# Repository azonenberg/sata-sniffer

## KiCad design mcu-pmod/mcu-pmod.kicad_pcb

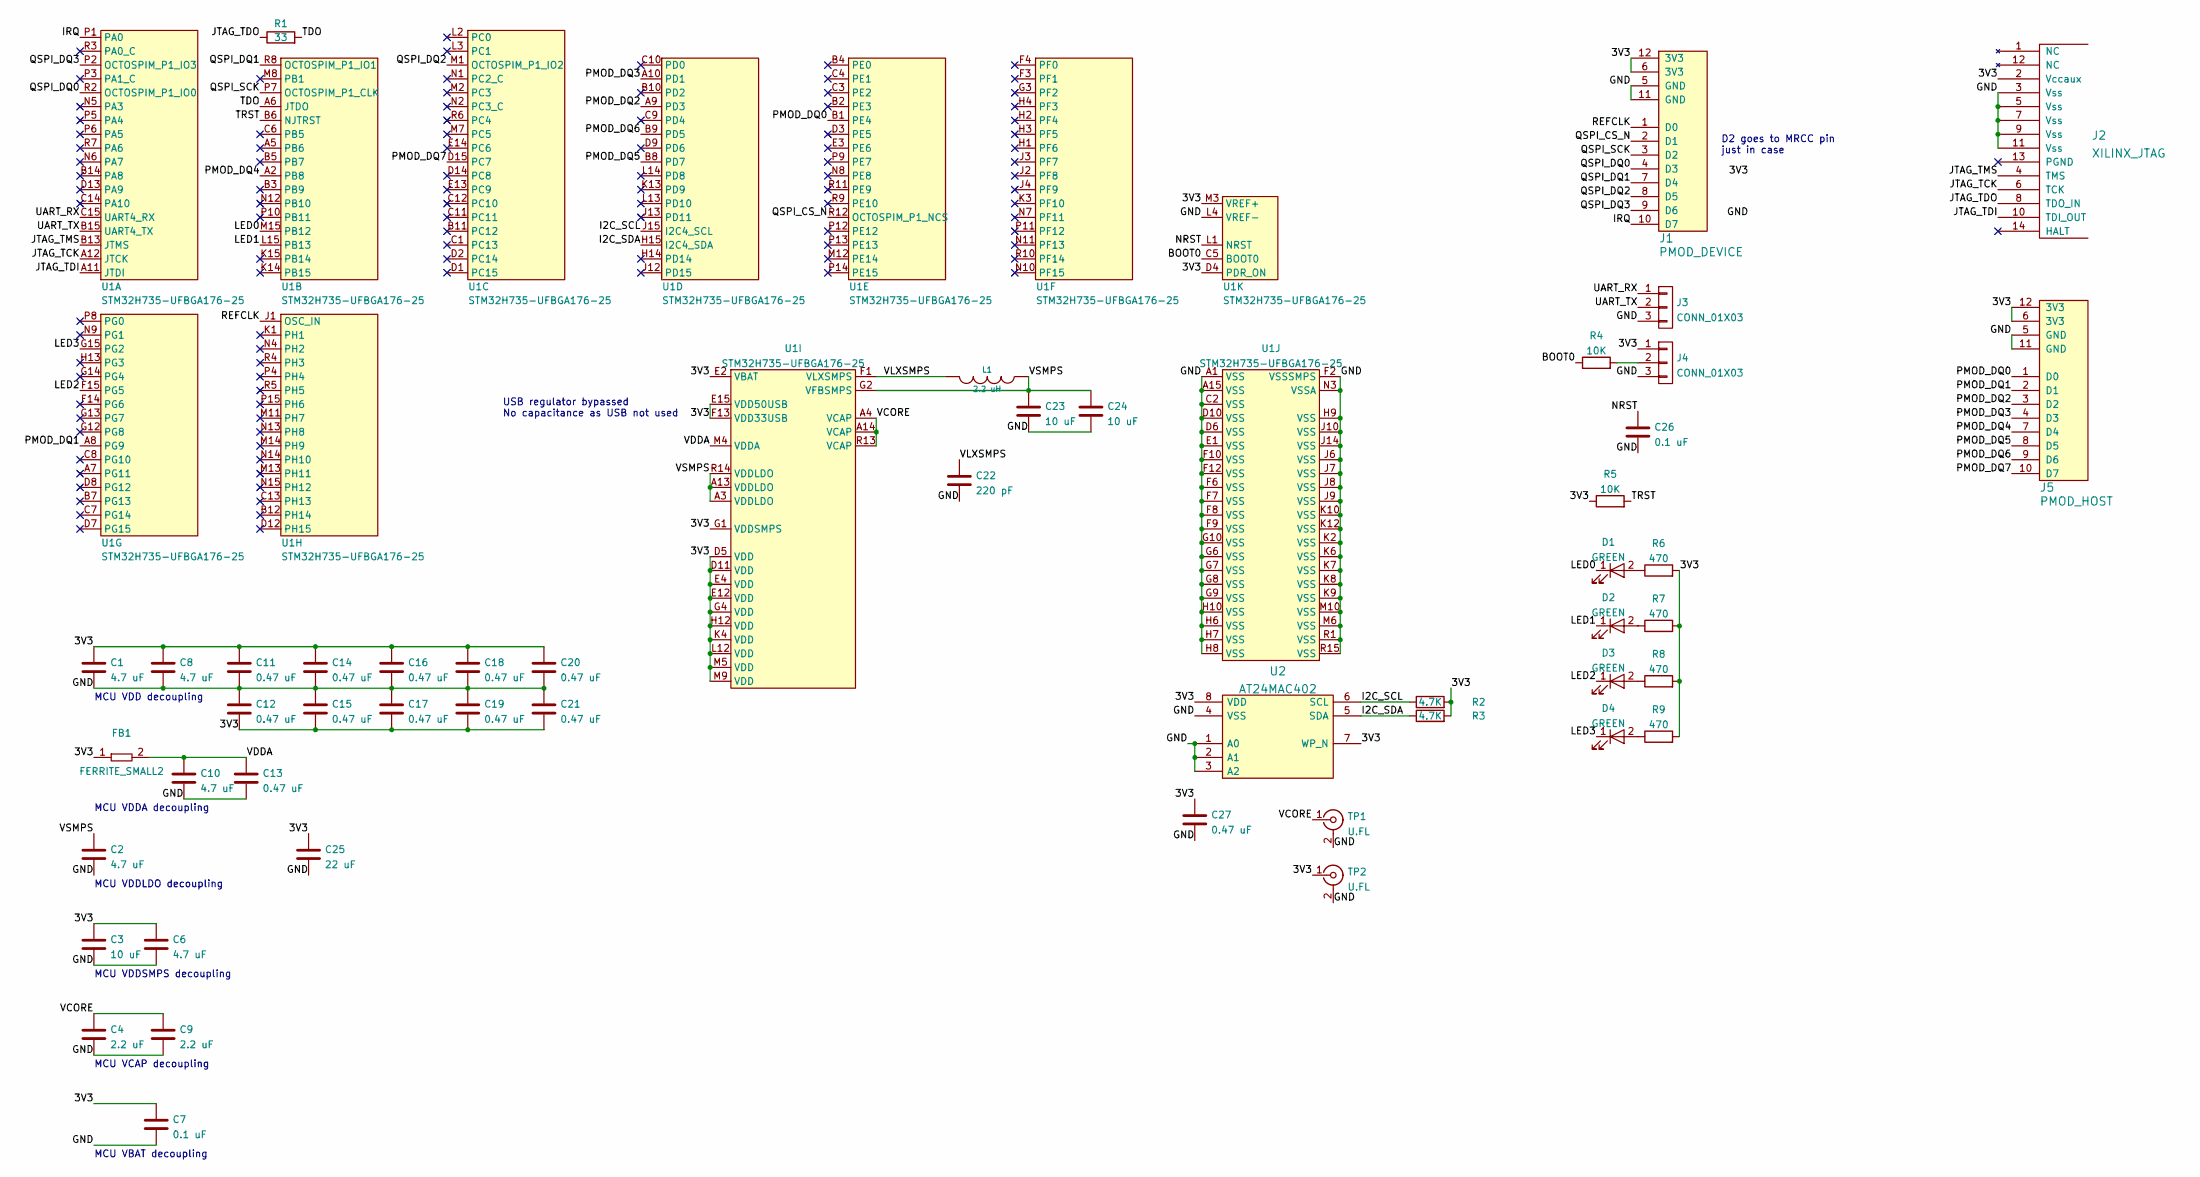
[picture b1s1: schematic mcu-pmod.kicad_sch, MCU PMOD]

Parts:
C1, C2, C6, C8, C10: 4.7 uF; EIA_0603_CAP_NOSILK
C3, C23, C24: 10 uF; EIA_0805_CAP_NOSILK
C4, C9: 2.2 uF; EIA_0603_CAP_NOSILK
C7, C26: 0.1 uF; EIA_0402_CAP_NOSILK
C11, C12, C13, C14, C15, C16, C17, C18, C19, C20, C21, C27: 0.47 uF; EIA_0402_CAP_NOSILK
C22: 220 pF; EIA_0402_CAP_NOSILK
C25: 22 uF; EIA_1206_CAP_NOSILK
D1, D2, D3, D4: GREEN; EIA_0805_LED
FB1: FERRITE_SMALL2; EIA_0603_INDUCTOR_NOSILK
J1: PMOD_DEVICE; CONN_HEADER_2.54MM_2x6_RA_PMOD_MODULE
J2: XILINX_JTAG; XILINX_JTAG_PTH_MOLEX_0878311420
J3, J4: CONN_01X03; CONN_HEADER_2.54MM_1x3
J5: PMOD_HOST; CONN_HEADER_2.54MM_2x6_RA_PMOD_HOST
L1: 2.2 uH; EIA_1210_CAP_NOSILK
R1: 33; EIA_0402_RES_NOSILK
R2, R3: 4.7K; EIA_0402_RES_NOSILK
R4, R5: 10K; EIA_0402_RES_NOSILK
R6, R7, R8, R9: 470; EIA_0402_RES_NOSILK
TP1, TP2: U.FL; CONN_U.FL_TE_1909763-1
U1: STM32H735-UFBGA176-25; BGA_201_10x10_DEPOP_0.65MM_OSHPARK
U2: AT24MAC402; DFN_8_0.5MM_2x3MM_TALL

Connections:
/3V3: C1.1, C3.1, C6.1, C7.1, C8.1, C11.1, C12.2, C14.1, C15.2, C16.1, C17.2, C18.1, C19.2, C20.1, C21.2, C25.1, C27.1, FB1.1, J1.6 (3V3), J1.12 (3V3), J2.2 (Vccaux), J4.1, J5.6 (3V3), J5.12 (3V3), R2.2, R3.2, R5.1, R6.2, R7.2, R8.2, R9.2, TP2.1 (In), U1.D4 (PDR_ON), U1.D5 (VDD), U1.D11 (VDD), U1.E2 (VBAT), U1.E4 (VDD), U1.E12 (VDD), U1.E15 (VDD50USB), U1.F13 (VDD33USB), U1.G1 (VDDSMPS), U1.G4 (VDD), U1.H12 (VDD), U1.K4 (VDD), U1.L12 (VDD), U1.M3 (VREF+), U1.M5 (VDD), U1.M9 (VDD), U2.7 (WP_N), U2.8 (VDD)
/BOOT0: R4.1, U1.C5 (BOOT0)
/GND: C1.2, C2.2, C3.2, C4.2, C6.2, C7.2, C8.2, C9.2, C10.2, C11.2, C12.1, C13.2, C14.2, C15.1, C16.2, C17.1, C18.2, C19.1, C20.2, C21.1, C22.2, C23.2, C24.2, C25.2, C26.2, C27.2, J1.5 (GND), J1.11 (GND), J2.3 (Vss), J2.5 (Vss), J2.7 (Vss), J2.9 (Vss), J2.11 (Vss), J3.3, J4.3, J5.5 (GND), J5.11 (GND), TP1.2 (Ext), TP2.2 (Ext), U1.A1 (VSS), U1.A15 (VSS), U1.C2 (VSS), U1.D6 (VSS), U1.D10 (VSS), U1.E1 (VSS), U1.F2 (VSSSMPS), U1.F6 (VSS), U1.F7 (VSS), U1.F8 (VSS), U1.F9 (VSS), U1.F10 (VSS), U1.F12 (VSS), U1.G6 (VSS), U1.G7 (VSS), U1.G8 (VSS), U1.G9 (VSS), U1.G10 (VSS), U1.H6 (VSS), U1.H7 (VSS), U1.H8 (VSS), U1.H9 (VSS), U1.H10 (VSS), U1.J6 (VSS), U1.J7 (VSS), U1.J8 (VSS), U1.J9 (VSS), U1.J10 (VSS), U1.J14 (VSS), U1.K2 (VSS), U1.K6 (VSS), U1.K7 (VSS), U1.K8 (VSS), U1.K9 (VSS), U1.K10 (VSS), U1.K12 (VSS), U1.L4 (VREF-), U1.M6 (VSS), U1.M10 (VSS), U1.N3 (VSSA), U1.R1 (VSS), U1.R15 (VSS), U2.1 (A0), U2.2 (A1), U2.3 (A2), U2.4 (VSS)
/I2C_SCL: R2.1, U1.J15 (I2C4_SCL), U2.6 (SCL)
/I2C_SDA: R3.1, U1.H15 (I2C4_SDA), U2.5 (SDA)
/IRQ: J1.10 (D7), U1.P1 (PA0)
/JTAG_TCK: J2.6 (TCK), U1.A12 (JTCK)
/JTAG_TDI: J2.10 (TDI_OUT), U1.A11 (JTDI)
/JTAG_TDO: J2.8 (TDO_IN), R1.1
/JTAG_TMS: J2.4 (TMS), U1.B13 (JTMS)
/LED0: D1.1 (K), U1.M15 (PB12)
/LED1: D2.1 (K), U1.L15 (PB13)
/LED2: D3.1 (K), U1.F15 (PG5)
/LED3: D4.1 (K), U1.G15 (PG2)
/NRST: C26.1, U1.L1 (NRST)
/PMOD_DQ0: J5.1 (D0), U1.B1 (PE4)
/PMOD_DQ1: J5.2 (D1), U1.A8 (PG9)
/PMOD_DQ2: J5.3 (D2), U1.A9 (PD3)
/PMOD_DQ3: J5.4 (D3), U1.A10 (PD1)
/PMOD_DQ4: J5.7 (D4), U1.A2 (PB8)
/PMOD_DQ5: J5.8 (D5), U1.B8 (PD7)
/PMOD_DQ6: J5.9 (D6), U1.B9 (PD5)
/PMOD_DQ7: J5.10 (D7), U1.D15 (PC7)
/QSPI_CS_N: J1.2 (D1), U1.R12 (OCTOSPIM_P1_NCS)
/QSPI_DQ0: J1.4 (D3), U1.R2 (OCTOSPIM_P1_IO0)
/QSPI_DQ1: J1.7 (D4), U1.R8 (OCTOSPIM_P1_IO1)
/QSPI_DQ2: J1.8 (D5), U1.M1 (OCTOSPIM_P1_IO2)
/QSPI_DQ3: J1.9 (D6), U1.P2 (OCTOSPIM_P1_IO3)
/QSPI_SCK: J1.3 (D2), U1.P7 (OCTOSPIM_P1_CLK)
/REFCLK: J1.1 (D0), U1.J1 (OSC_IN)
/TDO: R1.2, U1.A6 (JTDO)
/TRST: R5.2, U1.B6 (NJTRST)
/UART_RX: J3.1, U1.C15 (UART4_RX)
/UART_TX: J3.2, U1.B15 (UART4_TX)
/VCORE: C4.1, C9.1, TP1.1 (In), U1.A4 (VCAP), U1.A14 (VCAP), U1.R13 (VCAP)
/VDDA: C10.1, C13.1, FB1.2, U1.M4 (VDDA)
/VLXSMPS: C22.1, L1.2, U1.F1 (VLXSMPS)
/VSMPS: C2.1, C23.1, C24.1, L1.1, U1.A3 (VDDLDO), U1.A13 (VDDLDO), U1.G2 (VFBSMPS), U1.R14 (VDDLDO)
unnamed: D1.2 (A), R6.1
unnamed: D2.2 (A), R7.1
unnamed: D3.2 (A), R8.1
unnamed: D4.2 (A), R9.1
unnamed: J4.2, R4.2

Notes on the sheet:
MCU VDDA decoupling
D2 goes to MRCC pin just in case
USB regulator bypassed No capacitance as USB not used
MCU VDDSMPS decoupling
MCU VCAP decoupling
MCU VDD decoupling
MCU VDDLDO decoupling
MCU VBAT decoupling

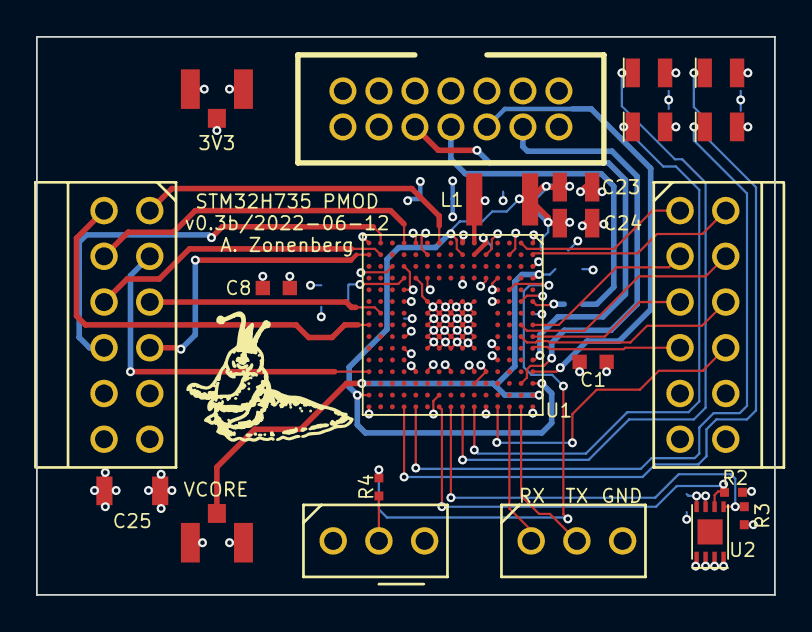
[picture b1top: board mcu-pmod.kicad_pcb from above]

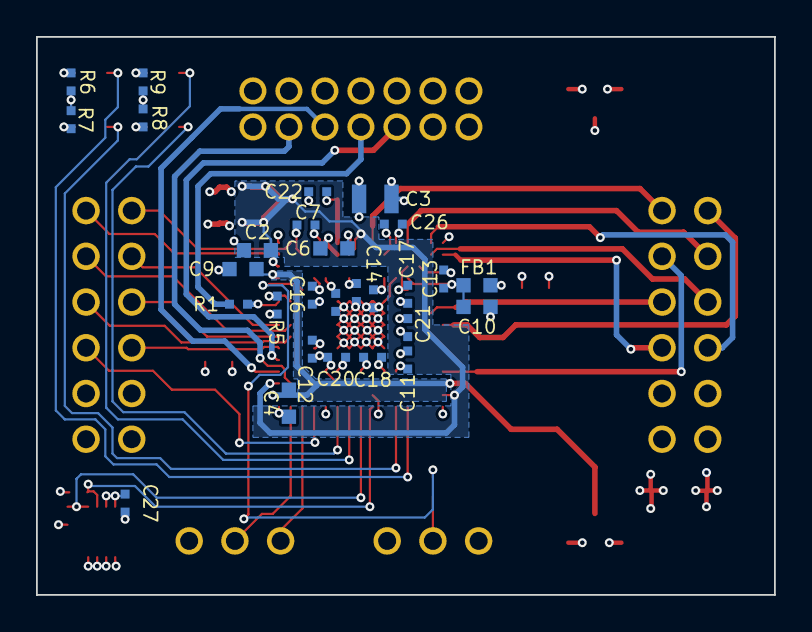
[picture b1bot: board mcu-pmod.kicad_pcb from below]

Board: 4 copper layers, 41.0 x 31.0 mm, 50 parts (28 on the bottom side), 43 nets.

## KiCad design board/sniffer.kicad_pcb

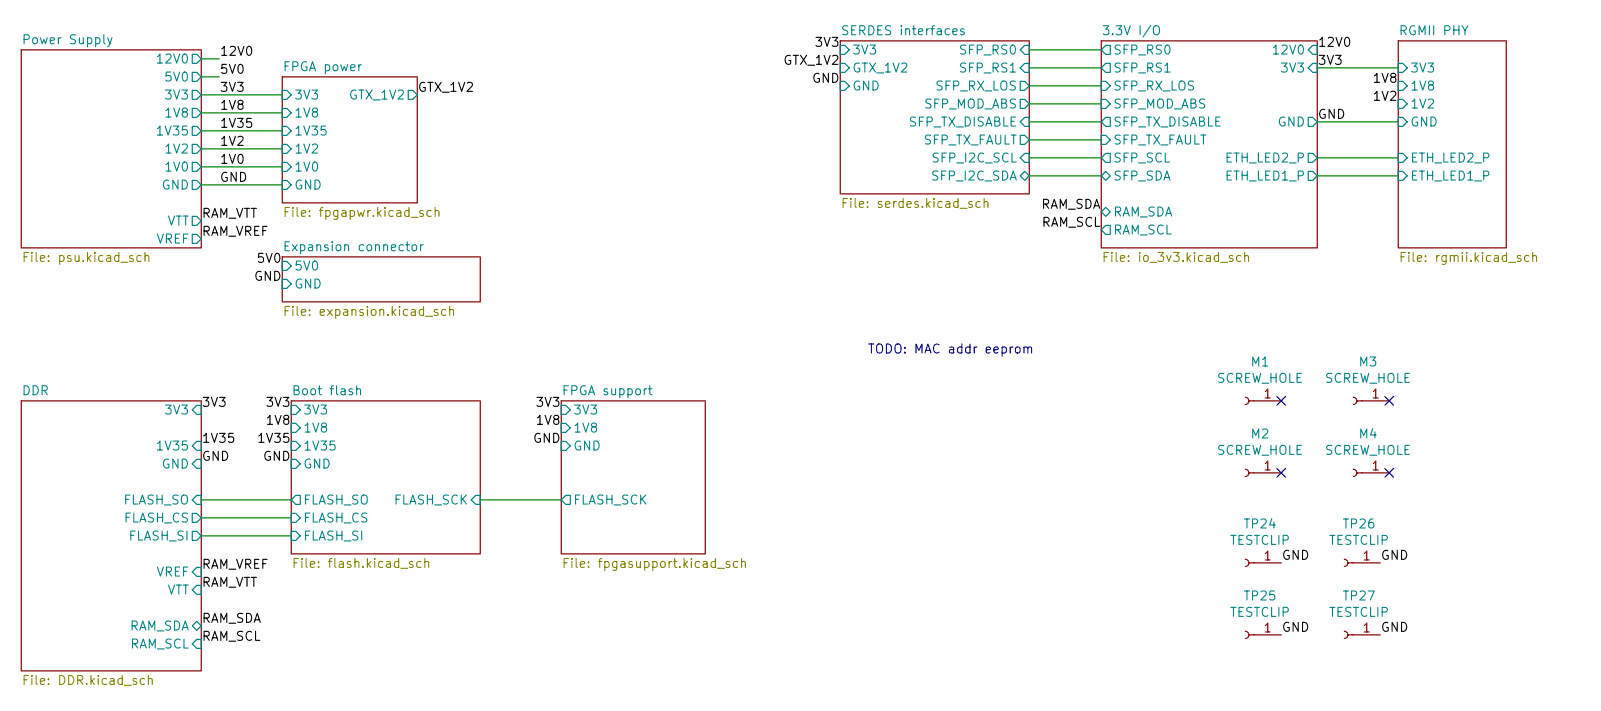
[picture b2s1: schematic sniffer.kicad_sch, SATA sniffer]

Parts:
M1, M2, M3, M4: SCREW_HOLE; MECHANICAL_CLEARANCEHOLE_4_40
TP24, TP25, TP26, TP27: TESTCLIP; TESTPOINT_SMT_KEYSTONE_5016

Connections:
unnamed: TP24.1, TP25.1, TP26.1, TP27.1

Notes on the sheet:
TODO: MAC addr eeprom

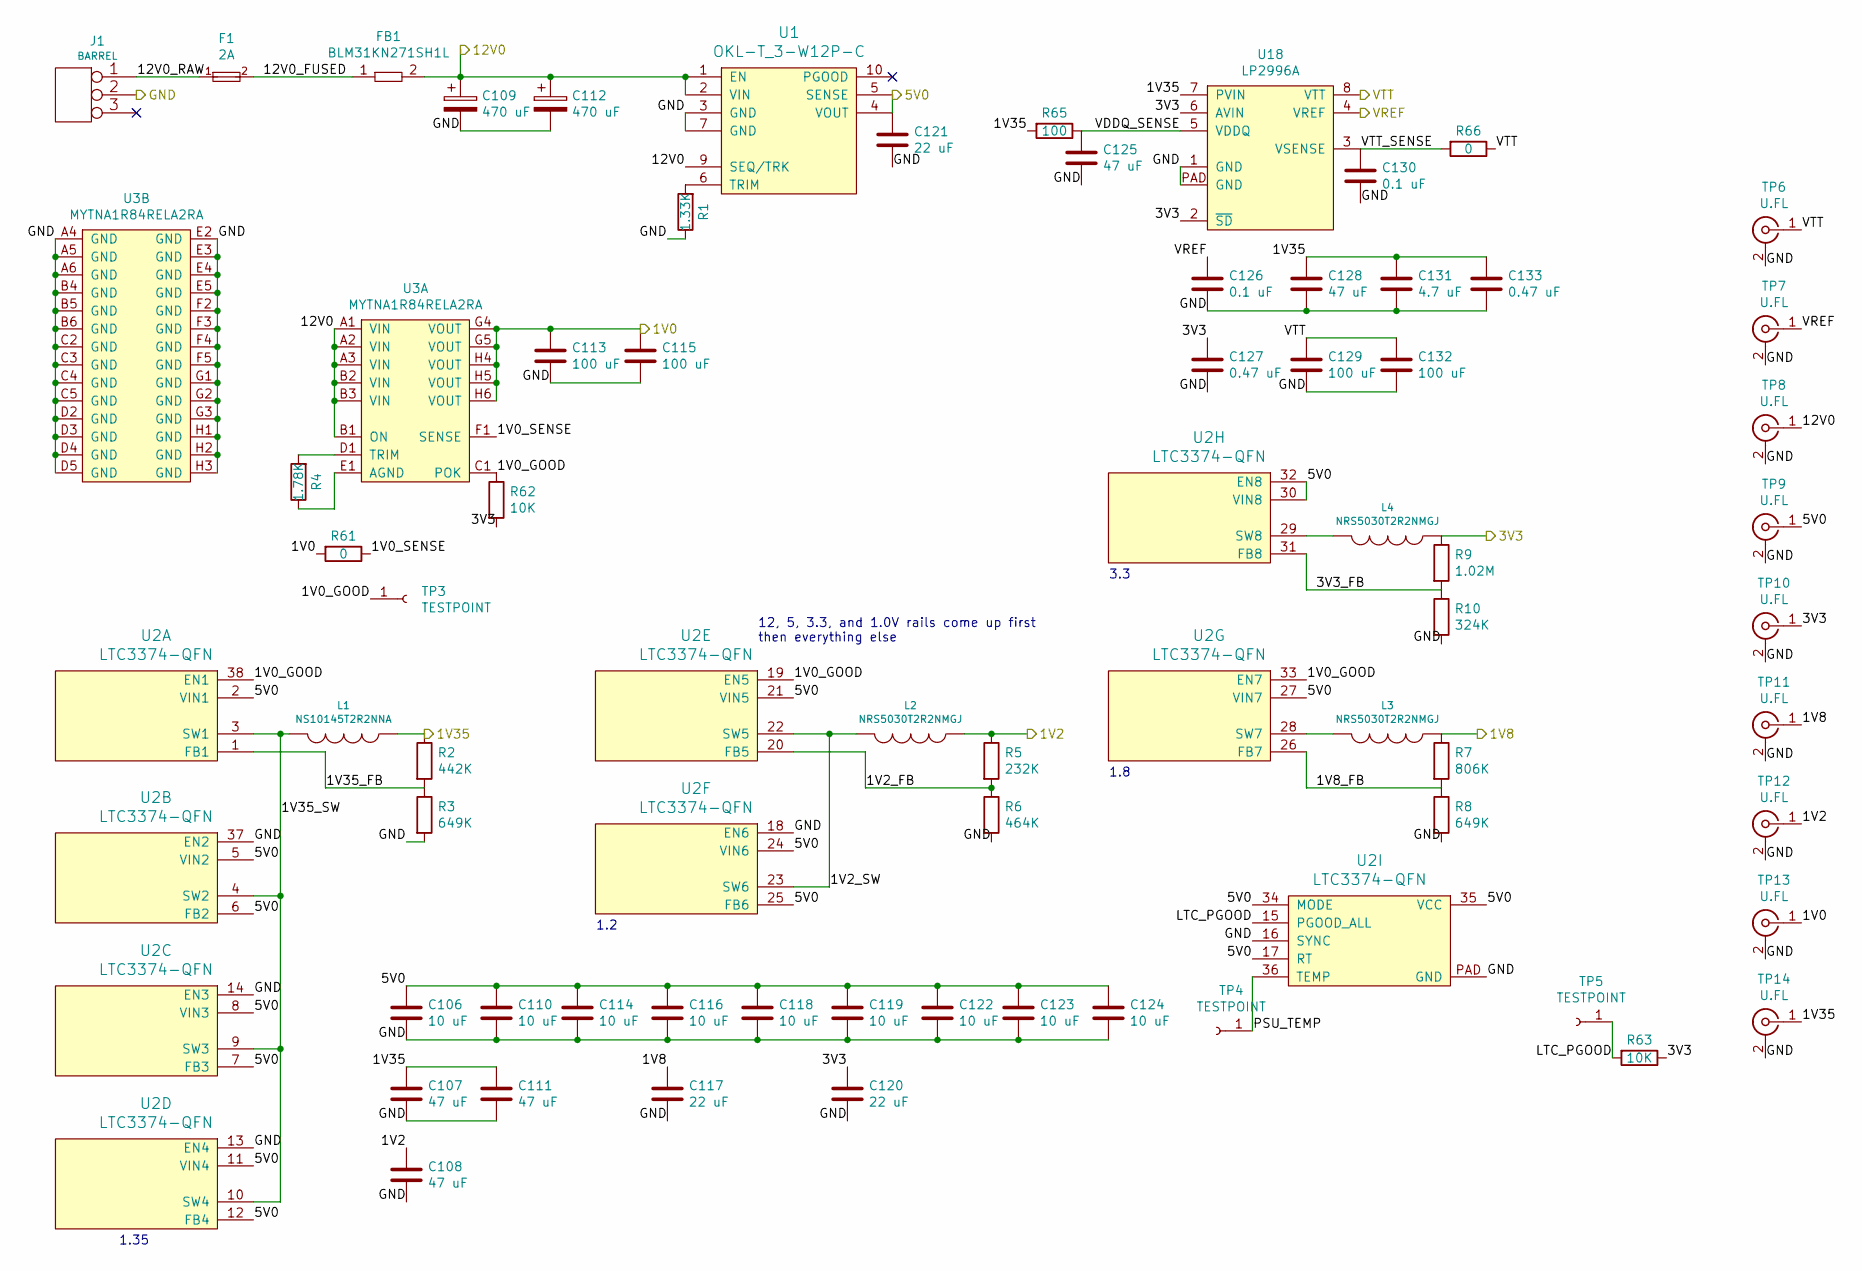
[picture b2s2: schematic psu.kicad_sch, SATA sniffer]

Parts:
C106, C110, C114, C116, C118, C119, C122, C123, C124: 10 uF; EIA_1210_CAP_NOSILK
C107, C108, C111, C125: 47 uF; EIA_0805_CAP_NOSILK
C109, C112: 470 uF; CAP_AL_10MM_SMT
C113, C115, C129, C132: 100 uF; EIA_1210_CAP_NOSILK
C117: 22 uF; EIA_0805_CAP_NOSILK
C120: 22 uF; EIA_1210_CAP_NOSILK
C121: 22 uF; EIA_1812_CAP_NOSILK
C126, C130: 0.1 uF; EIA_0402_CAP_NOSILK
C127, C133: 0.47 uF; EIA_0402_CAP_NOSILK
C128: 47 uF; EIA_1206_CAP_NOSILK
C131: 4.7 uF; EIA_0603_CAP_NOSILK
F1: 2A; EIA_0603_CAP_NOSILK
FB1: BLM31KN271SH1L; EIA_1206_CAP_NOSILK
J1: BARREL; CONN_CUI_PJ-058BH_HIPWR_BARREL_NOSLOT
L1: NS10145T2R2NNA; INDUCTOR_YUDEN_LSRN_10145
L2, L3, L4: NRS5030T2R2NMGJ; INDUCTOR_YUDEN_NRS5030
R1: 1.33K; EIA_0402_RES_NOSILK
R2: 442K; EIA_0402_RES_NOSILK
R3, R8: 649K; EIA_0402_RES_NOSILK
R4: 1.78K; EIA_0402_RES_NOSILK
R5: 232K; EIA_0402_RES_NOSILK
R6: 464K; EIA_0402_RES_NOSILK
R7: 806K; EIA_0402_RES_NOSILK
R9: 1.02M; EIA_0402_RES_NOSILK
R10: 324K; EIA_0402_RES_NOSILK
R61, R66: 0; EIA_0402_RES_NOSILK
R62, R63: 10K; EIA_0402_RES_NOSILK
R65: 100; EIA_0402_RES_NOSILK
TP3, TP4, TP5: TESTPOINT; TESTPOINT_SMT_0.5MM
TP6, TP7, TP8, TP9, TP10, TP11, TP12, TP13, TP14: U.FL; CONN_U.FL_TE_1909763-1
U1: OKL-T_3-W12P-C; MODULE_MURATA_OKL-T3-W12
U2: LTC3374-QFN; QFN_38_0.5MM_5x7MM
U3: MYTNA1R84RELA2RA; MODULE_MURATA_MYTNA1R84RELA2RA
U18: LP2996A; SOIC_8_3.9MM_EPAD

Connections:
/1V0: C113.1, C115.1, R61.2, TP13.1 (In), U3.G4 (VOUT), U3.G5 (VOUT), U3.H4 (VOUT), U3.H5 (VOUT), U3.H6 (VOUT); also elsewhere on the board
/1V2: C108.1, L2.1, R5.1, TP12.1 (In); also elsewhere on the board
/1V8: C117.1, L3.1, R7.1, TP11.1 (In); also elsewhere on the board
/1V35: C107.1, C111.1, C128.1, C131.1, C133.1, L1.1, R2.1, R65.2, TP14.1 (In), U18.7 (PVIN); also elsewhere on the board
/3V3: C120.1, C127.1, L4.1, R9.1, R62.2, R63.1, TP10.1 (In), U18.2 (~SD), U18.6 (AVIN); also elsewhere on the board
/5V0: C106.1, C110.1, C114.1, C116.1, C118.1, C119.1, C121.1, C122.1, C123.1, C124.1, TP9.1 (In), U1.4 (VOUT), U1.5 (SENSE), U2.2 (VIN1), U2.5 (VIN2), U2.6 (FB2), U2.7 (FB3), U2.8 (VIN3), U2.11 (VIN4), U2.12 (FB4), U2.17 (RT), U2.21 (VIN5), U2.24 (VIN6), U2.25 (FB6), U2.27 (VIN7), U2.30 (VIN8), U2.32 (EN8), U2.34 (MODE), U2.35 (VCC); also elsewhere on the board
/12V0: C109.1, C112.1, FB1.2, TP8.1 (In), U1.1 (EN), U1.2 (VIN), U1.9 (SEQ/TRK), U3.A1 (VIN), U3.A2 (VIN), U3.A3 (VIN), U3.B1 (ON), U3.B2 (VIN), U3.B3 (VIN); also elsewhere on the board
/Power Supply/1V0_GOOD: R62.1, TP3.1, U2.19 (EN5), U2.33 (EN7), U2.38 (EN1), U3.C1 (POK)
/Power Supply/1V0_SENSE: R61.1, U3.F1 (SENSE)
/Power Supply/1V2_FB: R5.2, R6.1, U2.20 (FB5)
/Power Supply/1V2_SW: L2.2, U2.22 (SW5), U2.23 (SW6)
/Power Supply/1V8_FB: R7.2, R8.1, U2.26 (FB7)
/Power Supply/1V35_FB: R2.2, R3.1, U2.1 (FB1)
/Power Supply/1V35_SW: L1.2, U2.3 (SW1), U2.4 (SW2), U2.9 (SW3), U2.10 (SW4)
/Power Supply/3V3_FB: R9.2, R10.1, U2.31 (FB8)
/Power Supply/12V0_FUSED: F1.2, FB1.1
/Power Supply/12V0_RAW: F1.1, J1.1
/Power Supply/LTC_PGOOD: R63.2, TP5.1, U2.15 (PGOOD_ALL)
/Power Supply/PSU_TEMP: TP4.1, U2.36 (TEMP)
/Power Supply/VDDQ_SENSE: C125.1, R65.1, U18.5 (VDDQ)
/Power Supply/VTT_SENSE: C130.1, R66.2, U18.3 (VSENSE)
/RAM_VREF: C126.1, TP7.1 (In), U18.4 (VREF); also elsewhere on the board
/RAM_VTT: C129.1, C132.1, R66.1, TP6.1 (In), U18.8 (VTT); also elsewhere on the board
unnamed: L3.2, U2.28 (SW7)
unnamed: L4.2, U2.29 (SW8)
unnamed: R1.2, U1.6 (TRIM)
unnamed: R4.1, U3.E1 (AGND)
unnamed: R4.2, U3.D1 (TRIM)

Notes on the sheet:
12, 5, 3.3, and 1.0V rails come up first then everything else
1.8
1.2
3.3
1.35

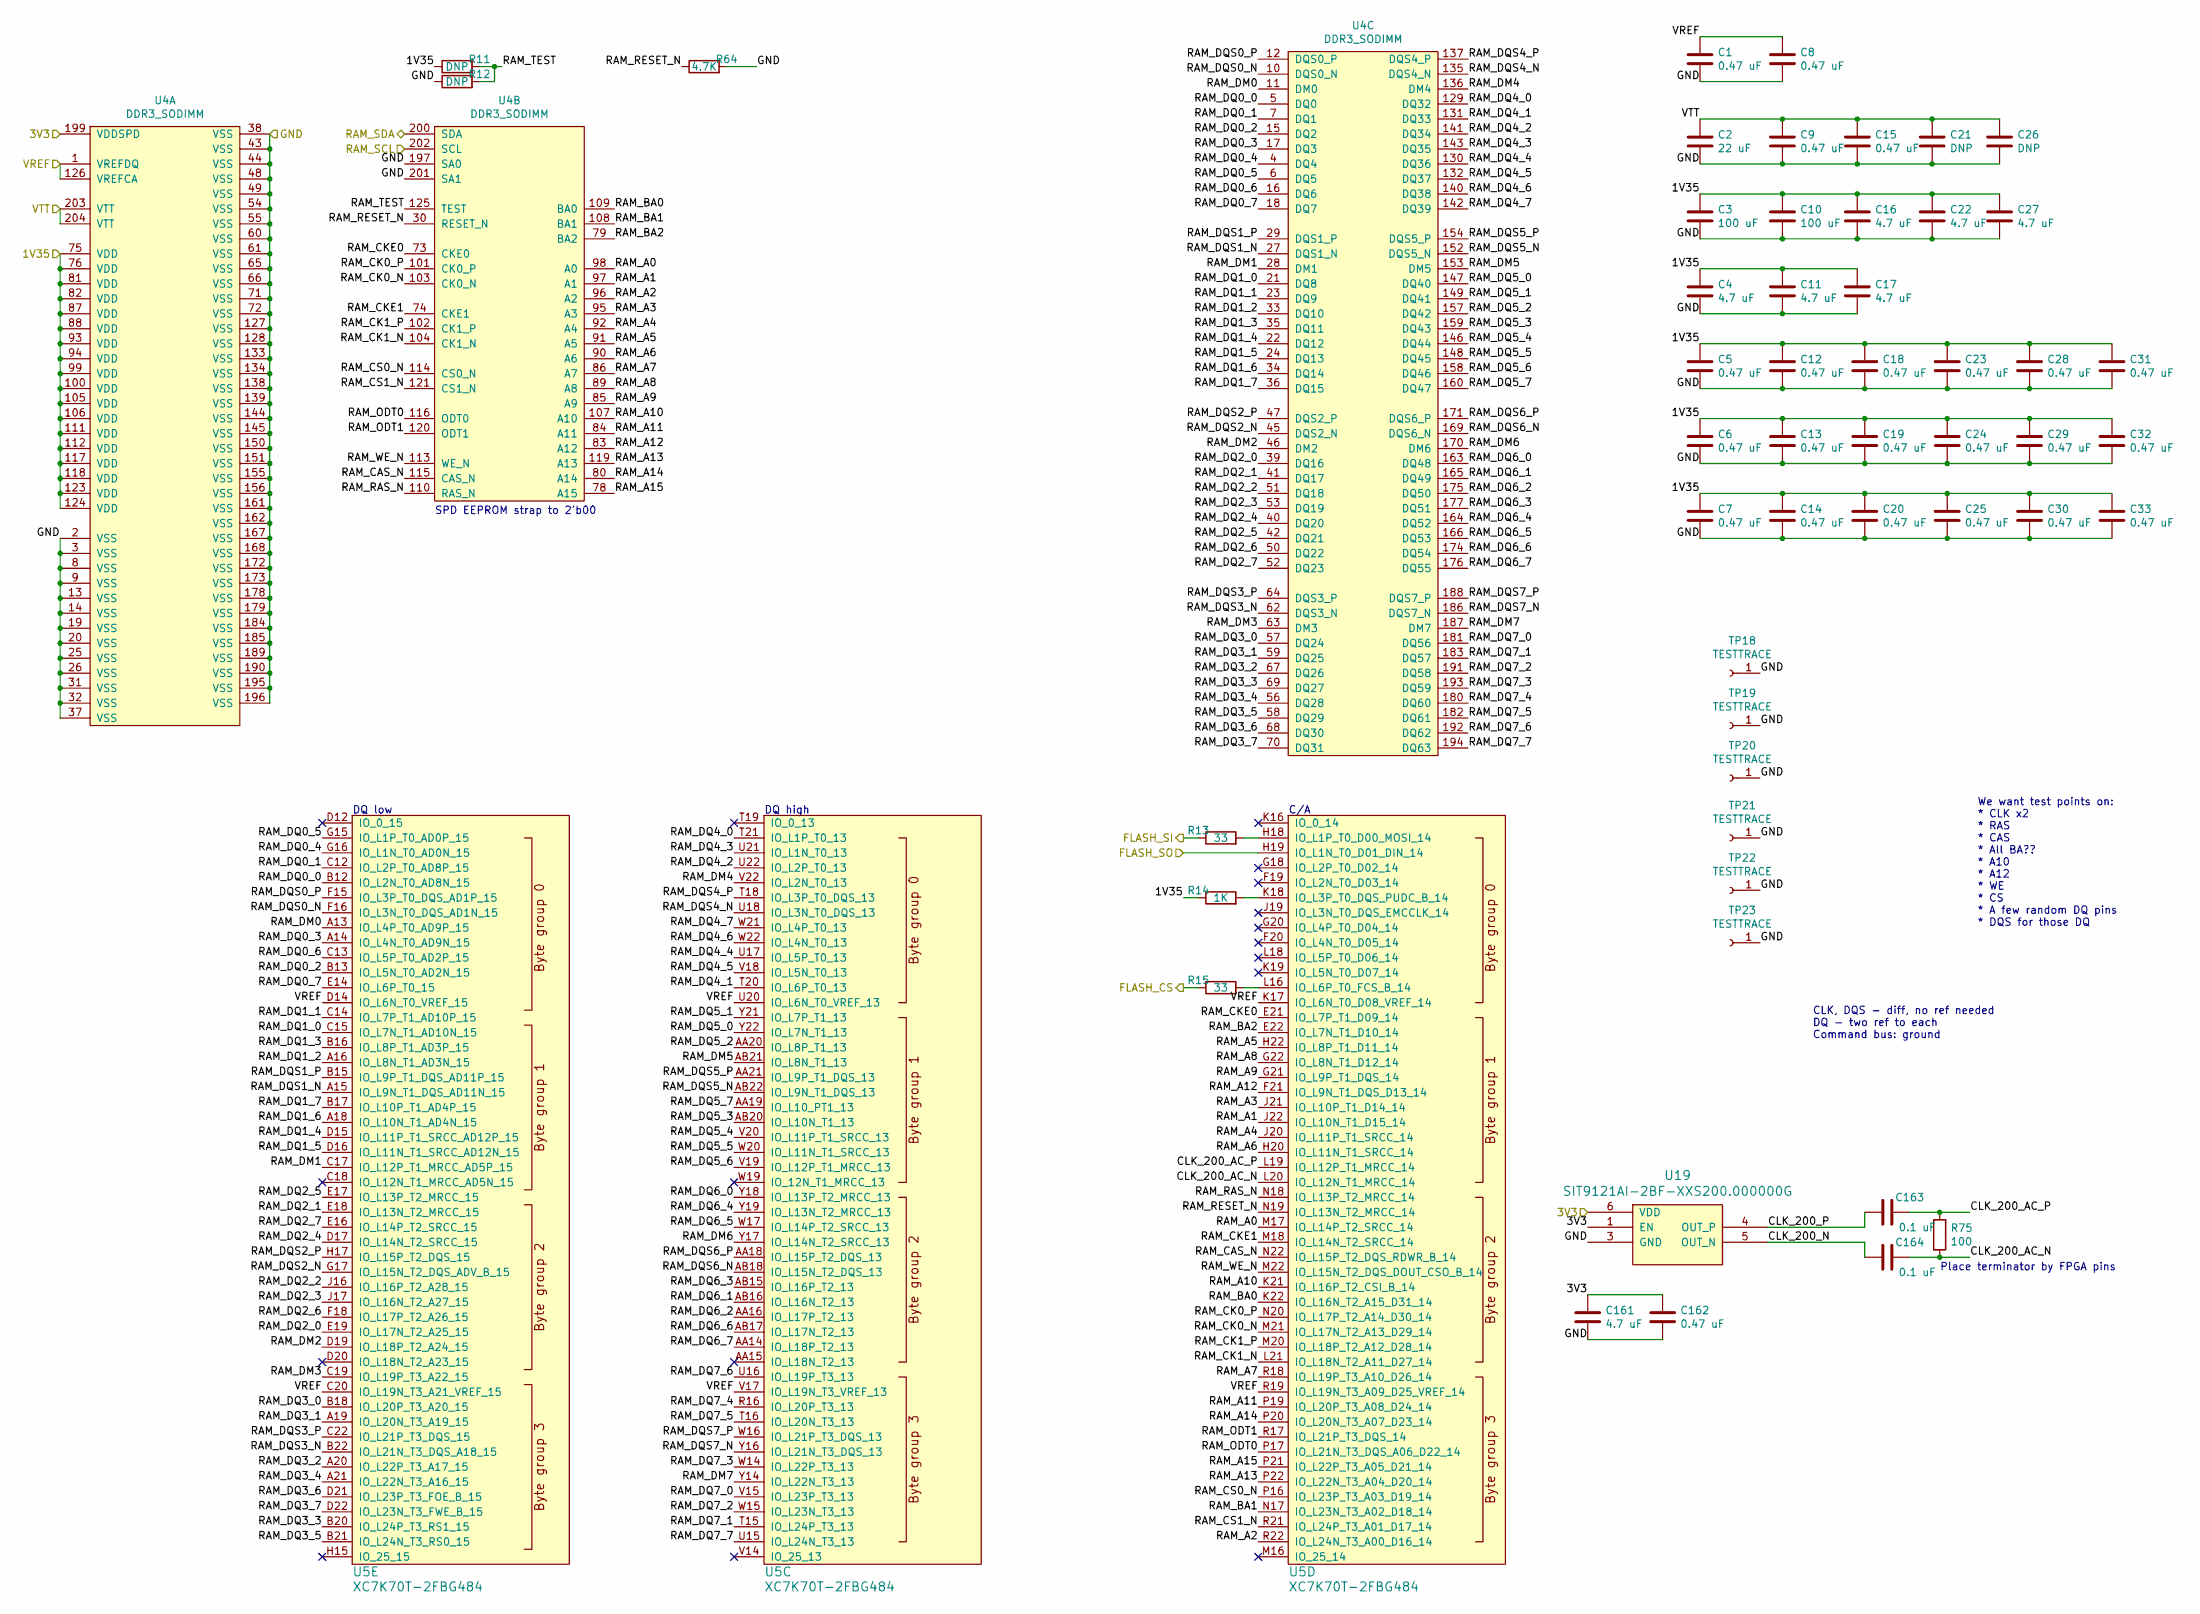
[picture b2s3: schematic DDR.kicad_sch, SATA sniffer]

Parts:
C1, C5, C6, C7, C8, C9, C12, C13, C14, C15, C18, C19, C20, C23, C24, C25, C28, C29, C30, C31, C32, C33, C162: 0.47 uF; EIA_0402_CAP_NOSILK
C2: 22 uF; EIA_0805_CAP_NOSILK
C3, C10: 100 uF; EIA_1206_CAP_NOSILK
C4, C11, C16, C17, C22, C27, C161: 4.7 uF; EIA_0603_CAP_NOSILK
C21, C26: DNP; EIA_0603_CAP_NOSILK
C163, C164: 0.1 uF; EIA_0402_CAP_NOSILK
R11, R12: DNP; EIA_0402_RES_NOSILK
R13, R15: 33; EIA_0402_RES_NOSILK
R14: 1K; EIA_0402_RES_NOSILK
R64: 4.7K; EIA_0402_RES_NOSILK
R75: 100; EIA_0402_RES_NOSILK
TP18, TP19, TP20, TP21, TP22, TP23: TESTTRACE; TESTPOINT_BARETRACE_150UM
U4: DDR3_SODIMM; CONN_SODIMM_DDR3_TE_2013289-1
U5: XC7K70T-2FBG484; BGA_484_22x22_FULLARRAY_1MM
U19: SIT9121AI-2BF-XXS200.000000G; OSCILLATOR_LVDS_3.2x2.5

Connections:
/1V35: C3.1, C4.1, C5.1, C6.1, C7.1, C10.1, C11.1, C12.1, C13.1, C14.1, C16.1, C17.1, C18.1, C19.1, C20.1, C22.1, C23.1, C24.1, C25.1, C27.1, C28.1, C29.1, C30.1, C31.1, C32.1, C33.1, R11.1, R14.1, U4.75 (VDD), U4.76 (VDD), U4.81 (VDD), U4.82 (VDD), U4.87 (VDD), U4.88 (VDD), U4.93 (VDD), U4.94 (VDD), U4.99 (VDD), U4.100 (VDD), U4.105 (VDD), U4.106 (VDD), U4.111 (VDD), U4.112 (VDD), U4.117 (VDD), U4.118 (VDD), U4.123 (VDD), U4.124 (VDD); also elsewhere on the board
/3V3: C161.1, C162.1, U4.199 (VDDSPD), U19.1 (EN), U19.6 (VDD); also elsewhere on the board
/Boot flash/FLASH_CS: R15.1; also elsewhere on the board
/Boot flash/FLASH_SI: R13.1; also elsewhere on the board
/Boot flash/FLASH_SO: U5.H19 (IO_L1N_T0_D01_DIN_14); also elsewhere on the board
/DDR/CLK_200_AC_N: C164.1, R75.2, U5.L20 (IO_L12N_T1_MRCC_14)
/DDR/CLK_200_AC_P: C163.1, R75.1, U5.L19 (IO_L12P_T1_MRCC_14)
/DDR/CLK_200_N: C164.2, U19.5 (OUT_N)
/DDR/CLK_200_P: C163.2, U19.4 (OUT_P)
/DDR/RAM_A0: U4.98 (A0), U5.M17 (IO_L14P_T2_SRCC_14)
/DDR/RAM_A1: U4.97 (A1), U5.J22 (IO_L10N_T1_D15_14)
/DDR/RAM_A2: U4.96 (A2), U5.R22 (IO_L24N_T3_A00_D16_14)
/DDR/RAM_A3: U4.95 (A3), U5.J21 (IO_L10P_T1_D14_14)
/DDR/RAM_A4: U4.92 (A4), U5.J20 (IO_L11P_T1_SRCC_14)
/DDR/RAM_A5: U4.91 (A5), U5.H22 (IO_L8P_T1_D11_14)
/DDR/RAM_A6: U4.90 (A6), U5.H20 (IO_L11N_T1_SRCC_14)
/DDR/RAM_A7: U4.86 (A7), U5.R18 (IO_L19P_T3_A10_D26_14)
/DDR/RAM_A8: U4.89 (A8), U5.G22 (IO_L8N_T1_D12_14)
/DDR/RAM_A9: U4.85 (A9), U5.G21 (IO_L9P_T1_DQS_14)
/DDR/RAM_A10: U4.107 (A10), U5.K21 (IO_L16P_T2_CSI_B_14)
/DDR/RAM_A11: U4.84 (A11), U5.P19 (IO_L20P_T3_A08_D24_14)
/DDR/RAM_A12: U4.83 (A12), U5.F21 (IO_L9N_T1_DQS_D13_14)
/DDR/RAM_A13: U4.119 (A13), U5.P22 (IO_L22N_T3_A04_D20_14)
/DDR/RAM_A14: U4.80 (A14), U5.P20 (IO_L20N_T3_A07_D23_14)
/DDR/RAM_A15: U4.78 (A15), U5.P21 (IO_L22P_T3_A05_D21_14)
/DDR/RAM_BA0: U4.109 (BA0), U5.K22 (IO_L16N_T2_A15_D31_14)
/DDR/RAM_BA1: U4.108 (BA1), U5.N17 (IO_L23N_T3_A02_D18_14)
/DDR/RAM_BA2: U4.79 (BA2), U5.E22 (IO_L7N_T1_D10_14)
/DDR/RAM_CAS_N: U4.115 (CAS_N), U5.N22 (IO_L15P_T2_DQS_RDWR_B_14)
/DDR/RAM_CK0_N: U4.103 (CK0_N), U5.M21 (IO_L17N_T2_A13_D29_14)
/DDR/RAM_CK0_P: U4.101 (CK0_P), U5.N20 (IO_L17P_T2_A14_D30_14)
/DDR/RAM_CK1_N: U4.104 (CK1_N), U5.L21 (IO_L18N_T2_A11_D27_14)
/DDR/RAM_CK1_P: U4.102 (CK1_P), U5.M20 (IO_L18P_T2_A12_D28_14)
/DDR/RAM_CKE0: U4.73 (CKE0), U5.E21 (IO_L7P_T1_D09_14)
/DDR/RAM_CKE1: U4.74 (CKE1), U5.M18 (IO_L14N_T2_SRCC_14)
/DDR/RAM_CS0_N: U4.114 (CS0_N), U5.P16 (IO_L23P_T3_A03_D19_14)
/DDR/RAM_CS1_N: U4.121 (CS1_N), U5.R21 (IO_L24P_T3_A01_D17_14)
/DDR/RAM_DM0: U4.11 (DM0), U5.A13 (IO_L4P_T0_AD9P_15)
/DDR/RAM_DM1: U4.28 (DM1), U5.C17 (IO_L12P_T1_MRCC_AD5P_15)
/DDR/RAM_DM2: U4.46 (DM2), U5.D19 (IO_L18P_T2_A24_15)
/DDR/RAM_DM3: U4.63 (DM3), U5.C19 (IO_L19P_T3_A22_15)
/DDR/RAM_DM4: U4.136 (DM4), U5.V22 (IO_L2N_T0_13)
/DDR/RAM_DM5: U4.153 (DM5), U5.AB21 (IO_L8N_T1_13)
/DDR/RAM_DM6: U4.170 (DM6), U5.Y17 (IO_L14N_T2_SRCC_13)
/DDR/RAM_DM7: U4.187 (DM7), U5.Y14 (IO_L22N_T3_13)
/DDR/RAM_DQ0_0: U4.5 (DQ0), U5.B12 (IO_L2N_T0_AD8N_15)
/DDR/RAM_DQ0_1: U4.7 (DQ1), U5.C12 (IO_L2P_T0_AD8P_15)
/DDR/RAM_DQ0_2: U4.15 (DQ2), U5.B13 (IO_L5N_T0_AD2N_15)
/DDR/RAM_DQ0_3: U4.17 (DQ3), U5.A14 (IO_L4N_T0_AD9N_15)
/DDR/RAM_DQ0_4: U4.4 (DQ4), U5.G16 (IO_L1N_T0_AD0N_15)
/DDR/RAM_DQ0_5: U4.6 (DQ5), U5.G15 (IO_L1P_T0_AD0P_15)
/DDR/RAM_DQ0_6: U4.16 (DQ6), U5.C13 (IO_L5P_T0_AD2P_15)
/DDR/RAM_DQ0_7: U4.18 (DQ7), U5.E14 (IO_L6P_T0_15)
/DDR/RAM_DQ1_0: U4.21 (DQ8), U5.C15 (IO_L7N_T1_AD10N_15)
/DDR/RAM_DQ1_1: U4.23 (DQ9), U5.C14 (IO_L7P_T1_AD10P_15)
/DDR/RAM_DQ1_2: U4.33 (DQ10), U5.A16 (IO_L8N_T1_AD3N_15)
/DDR/RAM_DQ1_3: U4.35 (DQ11), U5.B16 (IO_L8P_T1_AD3P_15)
/DDR/RAM_DQ1_4: U4.22 (DQ12), U5.D15 (IO_L11P_T1_SRCC_AD12P_15)
/DDR/RAM_DQ1_5: U4.24 (DQ13), U5.D16 (IO_L11N_T1_SRCC_AD12N_15)
/DDR/RAM_DQ1_6: U4.34 (DQ14), U5.A18 (IO_L10N_T1_AD4N_15)
/DDR/RAM_DQ1_7: U4.36 (DQ15), U5.B17 (IO_L10P_T1_AD4P_15)
/DDR/RAM_DQ2_0: U4.39 (DQ16), U5.E19 (IO_L17N_T2_A25_15)
/DDR/RAM_DQ2_1: U4.41 (DQ17), U5.E18 (IO_L13N_T2_MRCC_15)
/DDR/RAM_DQ2_2: U4.51 (DQ18), U5.J16 (IO_L16P_T2_A28_15)
/DDR/RAM_DQ2_3: U4.53 (DQ19), U5.J17 (IO_L16N_T2_A27_15)
/DDR/RAM_DQ2_4: U4.40 (DQ20), U5.D17 (IO_L14N_T2_SRCC_15)
/DDR/RAM_DQ2_5: U4.42 (DQ21), U5.E17 (IO_L13P_T2_MRCC_15)
/DDR/RAM_DQ2_6: U4.50 (DQ22), U5.F18 (IO_L17P_T2_A26_15)
/DDR/RAM_DQ2_7: U4.52 (DQ23), U5.E16 (IO_L14P_T2_SRCC_15)
/DDR/RAM_DQ3_0: U4.57 (DQ24), U5.B18 (IO_L20P_T3_A20_15)
/DDR/RAM_DQ3_1: U4.59 (DQ25), U5.A19 (IO_L20N_T3_A19_15)
/DDR/RAM_DQ3_2: U4.67 (DQ26), U5.A20 (IO_L22P_T3_A17_15)
/DDR/RAM_DQ3_3: U4.69 (DQ27), U5.B20 (IO_L24P_T3_RS1_15)
/DDR/RAM_DQ3_4: U4.56 (DQ28), U5.A21 (IO_L22N_T3_A16_15)
/DDR/RAM_DQ3_5: U4.58 (DQ29), U5.B21 (IO_L24N_T3_RS0_15)
/DDR/RAM_DQ3_6: U4.68 (DQ30), U5.D21 (IO_L23P_T3_FOE_B_15)
/DDR/RAM_DQ3_7: U4.70 (DQ31), U5.D22 (IO_L23N_T3_FWE_B_15)
/DDR/RAM_DQ4_0: U4.129 (DQ32), U5.T21 (IO_L1P_T0_13)
/DDR/RAM_DQ4_1: U4.131 (DQ33), U5.T20 (IO_L6P_T0_13)
/DDR/RAM_DQ4_2: U4.141 (DQ34), U5.U22 (IO_L2P_T0_13)
/DDR/RAM_DQ4_3: U4.143 (DQ35), U5.U21 (IO_L1N_T0_13)
/DDR/RAM_DQ4_4: U4.130 (DQ36), U5.U17 (IO_L5P_T0_13)
/DDR/RAM_DQ4_5: U4.132 (DQ37), U5.V18 (IO_L5N_T0_13)
/DDR/RAM_DQ4_6: U4.140 (DQ38), U5.W22 (IO_L4N_T0_13)
/DDR/RAM_DQ4_7: U4.142 (DQ39), U5.W21 (IO_L4P_T0_13)
/DDR/RAM_DQ5_0: U4.147 (DQ40), U5.Y22 (IO_L7N_T1_13)
/DDR/RAM_DQ5_1: U4.149 (DQ41), U5.Y21 (IO_L7P_T1_13)
/DDR/RAM_DQ5_2: U4.157 (DQ42), U5.AA20 (IO_L8P_T1_13)
/DDR/RAM_DQ5_3: U4.159 (DQ43), U5.AB20 (IO_L10N_T1_13)
/DDR/RAM_DQ5_4: U4.146 (DQ44), U5.V20 (IO_L11P_T1_SRCC_13)
/DDR/RAM_DQ5_5: U4.148 (DQ45), U5.W20 (IO_L11N_T1_SRCC_13)
/DDR/RAM_DQ5_6: U4.158 (DQ46), U5.V19 (IO_L12P_T1_MRCC_13)
/DDR/RAM_DQ5_7: U4.160 (DQ47), U5.AA19 (IO_L10_PT1_13)
/DDR/RAM_DQ6_0: U4.163 (DQ48), U5.Y18 (IO_L13P_T2_MRCC_13)
/DDR/RAM_DQ6_1: U4.165 (DQ49), U5.AB16 (IO_L16N_T2_13)
/DDR/RAM_DQ6_2: U4.175 (DQ50), U5.AA16 (IO_L17P_T2_13)
/DDR/RAM_DQ6_3: U4.177 (DQ51), U5.AB15 (IO_L16P_T2_13)
/DDR/RAM_DQ6_4: U4.164 (DQ52), U5.Y19 (IO_L13N_T2_MRCC_13)
/DDR/RAM_DQ6_5: U4.166 (DQ53), U5.W17 (IO_L14P_T2_SRCC_13)
/DDR/RAM_DQ6_6: U4.174 (DQ54), U5.AB17 (IO_L17N_T2_13)
/DDR/RAM_DQ6_7: U4.176 (DQ55), U5.AA14 (IO_L18P_T2_13)
/DDR/RAM_DQ7_0: U4.181 (DQ56), U5.V15 (IO_L23P_T3_13)
/DDR/RAM_DQ7_1: U4.183 (DQ57), U5.T15 (IO_L24P_T3_13)
/DDR/RAM_DQ7_2: U4.191 (DQ58), U5.W15 (IO_L23N_T3_13)
/DDR/RAM_DQ7_3: U4.193 (DQ59), U5.W14 (IO_L22P_T3_13)
/DDR/RAM_DQ7_4: U4.180 (DQ60), U5.R16 (IO_L20P_T3_13)
/DDR/RAM_DQ7_5: U4.182 (DQ61), U5.T16 (IO_L20N_T3_13)
/DDR/RAM_DQ7_6: U4.192 (DQ62), U5.U16 (IO_L19P_T3_13)
/DDR/RAM_DQ7_7: U4.194 (DQ63), U5.U15 (IO_L24N_T3_13)
/DDR/RAM_DQS0_N: U4.10 (DQS0_N), U5.F16 (IO_L3N_T0_DQS_AD1N_15)
/DDR/RAM_DQS0_P: U4.12 (DQS0_P), U5.F15 (IO_L3P_T0_DQS_AD1P_15)
/DDR/RAM_DQS1_N: U4.27 (DQS1_N), U5.A15 (IO_L9N_T1_DQS_AD11N_15)
/DDR/RAM_DQS1_P: U4.29 (DQS1_P), U5.B15 (IO_L9P_T1_DQS_AD11P_15)
/DDR/RAM_DQS2_N: U4.45 (DQS2_N), U5.G17 (IO_L15N_T2_DQS_ADV_B_15)
/DDR/RAM_DQS2_P: U4.47 (DQS2_P), U5.H17 (IO_L15P_T2_DQS_15)
/DDR/RAM_DQS3_N: U4.62 (DQS3_N), U5.B22 (IO_L21N_T3_DQS_A18_15)
/DDR/RAM_DQS3_P: U4.64 (DQS3_P), U5.C22 (IO_L21P_T3_DQS_15)
/DDR/RAM_DQS4_N: U4.135 (DQS4_N), U5.U18 (IO_L3N_T0_DQS_13)
/DDR/RAM_DQS4_P: U4.137 (DQS4_P), U5.T18 (IO_L3P_T0_DQS_13)
/DDR/RAM_DQS5_N: U4.152 (DQS5_N), U5.AB22 (IO_L9N_T1_DQS_13)
/DDR/RAM_DQS5_P: U4.154 (DQS5_P), U5.AA21 (IO_L9P_T1_DQS_13)
/DDR/RAM_DQS6_N: U4.169 (DQS6_N), U5.AB18 (IO_L15N_T2_DQS_13)
/DDR/RAM_DQS6_P: U4.171 (DQS6_P), U5.AA18 (IO_L15P_T2_DQS_13)
/DDR/RAM_DQS7_N: U4.186 (DQS7_N), U5.Y16 (IO_L21N_T3_DQS_13)
/DDR/RAM_DQS7_P: U4.188 (DQS7_P), U5.W16 (IO_L21P_T3_DQS_13)
/DDR/RAM_ODT0: U4.116 (ODT0), U5.P17 (IO_L21N_T3_DQS_A06_D22_14)
/DDR/RAM_ODT1: U4.120 (ODT1), U5.R17 (IO_L21P_T3_DQS_14)
/DDR/RAM_RAS_N: U4.110 (RAS_N), U5.N18 (IO_L13P_T2_MRCC_14)
/DDR/RAM_RESET_N: R64.1, U4.30 (RESET_N), U5.N19 (IO_L13N_T2_MRCC_14)
/DDR/RAM_TEST: R11.2, R12.2, U4.125 (TEST)
/DDR/RAM_WE_N: U4.113 (WE_N), U5.M22 (IO_L15N_T2_DQS_DOUT_CSO_B_14)
/RAM_SCL: U4.202 (SCL); also elsewhere on the board
/RAM_SDA: U4.200 (SDA); also elsewhere on the board
/RAM_VREF: C1.1, C8.1, U4.1 (VREFDQ), U4.126 (VREFCA), U5.C20 (IO_L19N_T3_A21_VREF_15), U5.D14 (IO_L6N_T0_VREF_15), U5.K17 (IO_L6N_T0_D08_VREF_14), U5.R19 (IO_L19N_T3_A09_D25_VREF_14), U5.U20 (IO_L6N_T0_VREF_13), U5.V17 (IO_L19N_T3_VREF_13); also elsewhere on the board
/RAM_VTT: C2.1, C9.1, C15.1, C21.1, C26.1, U4.203 (VTT), U4.204 (VTT); also elsewhere on the board
unnamed: R13.2, U5.H18 (IO_L1P_T0_D00_MOSI_14)
unnamed: R14.2, U5.K18 (IO_L3P_T0_DQS_PUDC_B_14)
unnamed: R15.2, U5.L16 (IO_L6P_T0_FCS_B_14)

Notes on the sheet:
SPD EEPROM strap to 2'b00
We want test points on: * CLK x2 * RAS * CAS * All BA?? * A10 * A12 * WE * CS * A few random DQ pins * DQS for those DQ
DQ high
C/A
Place terminator by FPGA pins
CLK, DQS - diff, no ref needed DQ - two ref to each Command bus: ground
DQ low

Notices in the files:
firmware/mcu-pmod/main.cpp:
Copyright (c) 2022 Andrew D. Zonenberg and contributors
All rights reserved.
